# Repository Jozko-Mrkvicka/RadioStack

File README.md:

TODO
====
- Software AVR:
	- Change folder structure in some more sensible way.
	- Polish header files + including.
	- I can`t include delay.h to other files than main one. Find out why and replace all workarounds.
	- Add keyword const to all function declarations where possible.
	- Add description to all functions and describe all input and output parameters.
	- Add description to all modules.
	- There is potential problem with settings of bits in registers to zero. I do it incorrectly. Fix it!!

- Eagle:
	- ADF:
		- Change ELMA encoder to "normal" (single) one.
		- Display will be selected with push button on encoder.
		- Decimal point will define which display is currently selected.
		- Adjust DWG accordingly
		- Draw first board.
		- Think about second board (find out how many more IO modules can be added to the address space).

- Buy:
	- Jumpers.
	- Female pin headers with long pins.

- Other ideas:
	- ELMA encoders not fully working in one NavComm module. Probably mechanically damaged. Fix it or resolder.
	- Holes for buttons and knobs on NavComm module are too small. This problem should be already fixed in Eagle/AutoCAD drawings but check it once again.
	- Change front panel to plastic one:
		- It will be thicker. 
		- Add couple of bolts + nuts to attach it firmly to the rest of a module. 
		- It will have also bevelled edges. 
	- Encoder push buttons in NavComm modules not enabled yet. Add them.
	- Change pin headers to another ones with longer pins to create more space between PCB boards. The reason is to create more space for bolts/nuts to attach the device to a box/cover.

- Unsorted legacy mess:
	SVN
	===
	- nahrat vsetky dokumenty z mejlov (a mozno aj mejly samotne) do zlozky Admin
	- pridat vsetky subory eagle.epf na ignor list

	AutoCAD
	=======
	- zistit preco je XPDR tmavsi ako ostatne casti
	- vypatrat ci existuje nieco ako globalne konstanty/parametre, aby som mohol pouzivat rovnaky rozmer vo viacerych vykresoch
	- (XPDR) pridat objekt "obycajny" prepinac (ako bol na starom transponderu)

	Eagle
	=====
	- (niektore) Konektory na doske NavCom_Board_1 a NavCom_Board_2 su vlozene do vrstvy TOP, ale v skutocnosti sa nachadzaju vzadu (BOTTOM). To sposobi ze pri vyrobe sa ich obrysy vytlacia na opacnej strane dosky (tPlaces vs. bPlaces). Preto je treba tieto suciastky prehodit (Mirror) do spravnej vrstvy. 
	- NavComm 2.1/Board 2 - tlacitka T1 az T4 - trojice dierok pre piny su velmi blizko pri sebe, tlacitko nechce zaliezt do dierok (opravit aj v AutoCADe)
	- (nav/comm) mozno by bolo dobre odstranit vyvody na tlacitko "S" z enkoderov ELMA
	- ku kazdemu enkoderu pridat 2 kondenzatory
	- prepisat popisky tlacitiek T1 az T4 na BTN1 az BTN4

	Programovanie
	=============
	- vysvetlit naco sluzi signal Latch Reset
	- presunut radiostack.h zo zlozky modules/include do common/includes, alebo daco podobne

	Kupit
	=====
	- Dutinková lišta BL810GD
	- este jednu Elmu + hmatniky
	- jumpery
	- MCP23016 (2x)
	- 279-RGP0207CHJ470M (16x odpor z Mouseru)
	- dual shaft/dual concentric enkoder (2 channels) - Mouser
	- doniest z domu ockovy kluc kvoli hmatniku na Elmu
	- 2x Avago HDSP-711E

	======================================================================
	// -c		 skompiluje zdrojak ".c" do objektoveho kodu ".o"
	// -Wall	 warning all
	// -pedantic
	// -o 		 pomenuje vystupny subor
	avr-gcc -c pokus.c -Wall -pedantic -o vystup.o

	// zkompiluje a zlinkuje do ".exe"
	avr-gcc pokus.c libkniznica.a

	// -q	quick append - zalozi archiv / prida ".o" subor do archivu
	avr-ar -q libfnc.a fnc3.o

	// -t	zobrazi vsetky ".o" subory v archive
	avr-ar -t libfnc.a

	// -d	delete - vymaze ".o" subor z archivu
	avr-ar -d libfnc.a fnc3.o

	// -p 	typ procesoru (m8, t13, t2313, ...)
	// -c 	typ programatoru (AVRispmkII)
	// -P 	port ku ktoremu je programator pripojeny (usb)
	// -U 	<typ pamate>:<zapis/citanie>:<subor>:<format dat>
	//		<typ pamate>	flash, eeprom, hfuse, lfuse
	//		<zapis/citanie>	r, w
	//		<subor>			nazov suboru, napr. pokus.hex
	//		<format dat>	i (intel)		
	avrdude -p m8 -c avrispmkii -P usb -U flash:w:pokus.hex:i

	avr-gcc -mmcu=atmega8 -o demo.o -c demo.c 
	avr-gcc -mmcu=atmega8 -o demo.elf demo.o
	avr-objcopy -j .text -j .data -O ihex flash.elf flash.hex

	avrdude -p m8 -c AVRispmkII -P usb -U lfuse:w:0xff:m
	avrdude -p m8 -c AVRispmkII -P usb -U hfuse:w:0xd9:m
	avrdude -p m8 -c AVRispmkII -P usb -U flash:w:bin/radiostack.hex:i

	/////////////////////////////////////////////////////////////
	// Timer/Counter Interrupt Mask Register
	// TIMSK = 0x01;

	// iba pokus
	// Timer/Counter Control Register
	// TCCR0 = 0x01;

	// iba pokus
	// Timer/Counter Register - initial value
	// TCNT0 = 0x00;

	ISR (INT0_vect)
	{
		interruption = 1;

		// overflow++;

		// if (overflow < 300)
		// 	inc = 5;

		// else if ((overflow >= 300) && (overflow < 400))
		// 	inc = 4;

		// else if ((overflow >= 400) && (overflow < 500))
		// 	inc = 3;

		// else if ((overflow >= 500) && (overflow < 600))
		// 	inc = 2;

		// else if ((overflow >= 600) /*&& (overflow < 600)*/)
		//  inc = 1;

		// overflow = 0;
	}

	// ISR (TIMER0_OVF_vect)
	// {
	// 	if (overflow < 2000)
	// 		overflow++;
	// }
	/////////////////////////////////////////////////////////////

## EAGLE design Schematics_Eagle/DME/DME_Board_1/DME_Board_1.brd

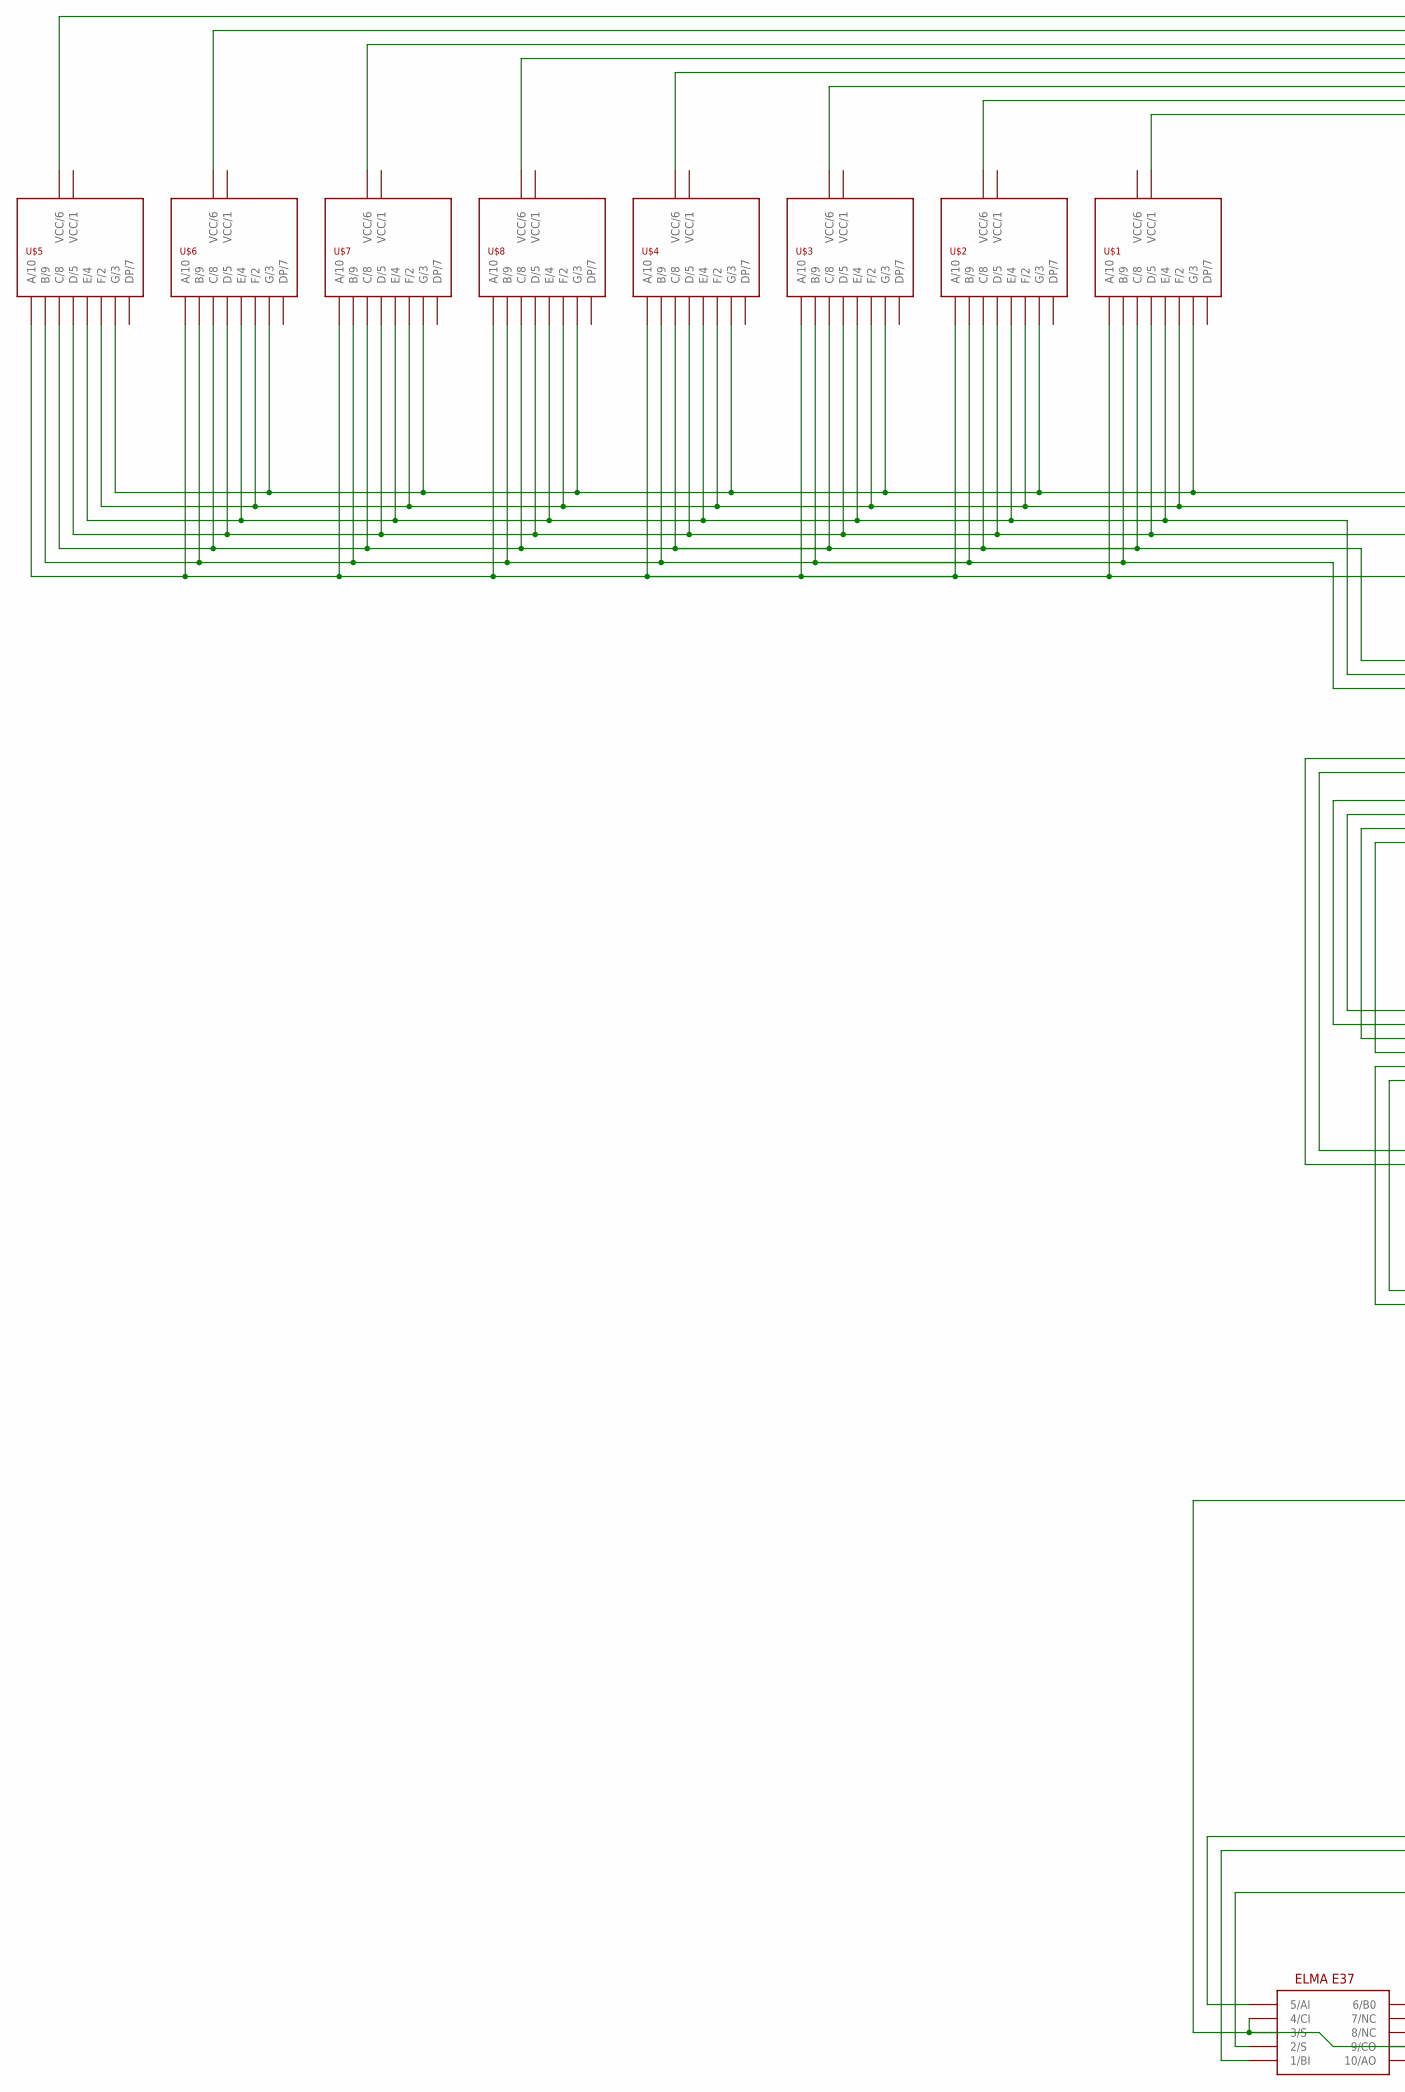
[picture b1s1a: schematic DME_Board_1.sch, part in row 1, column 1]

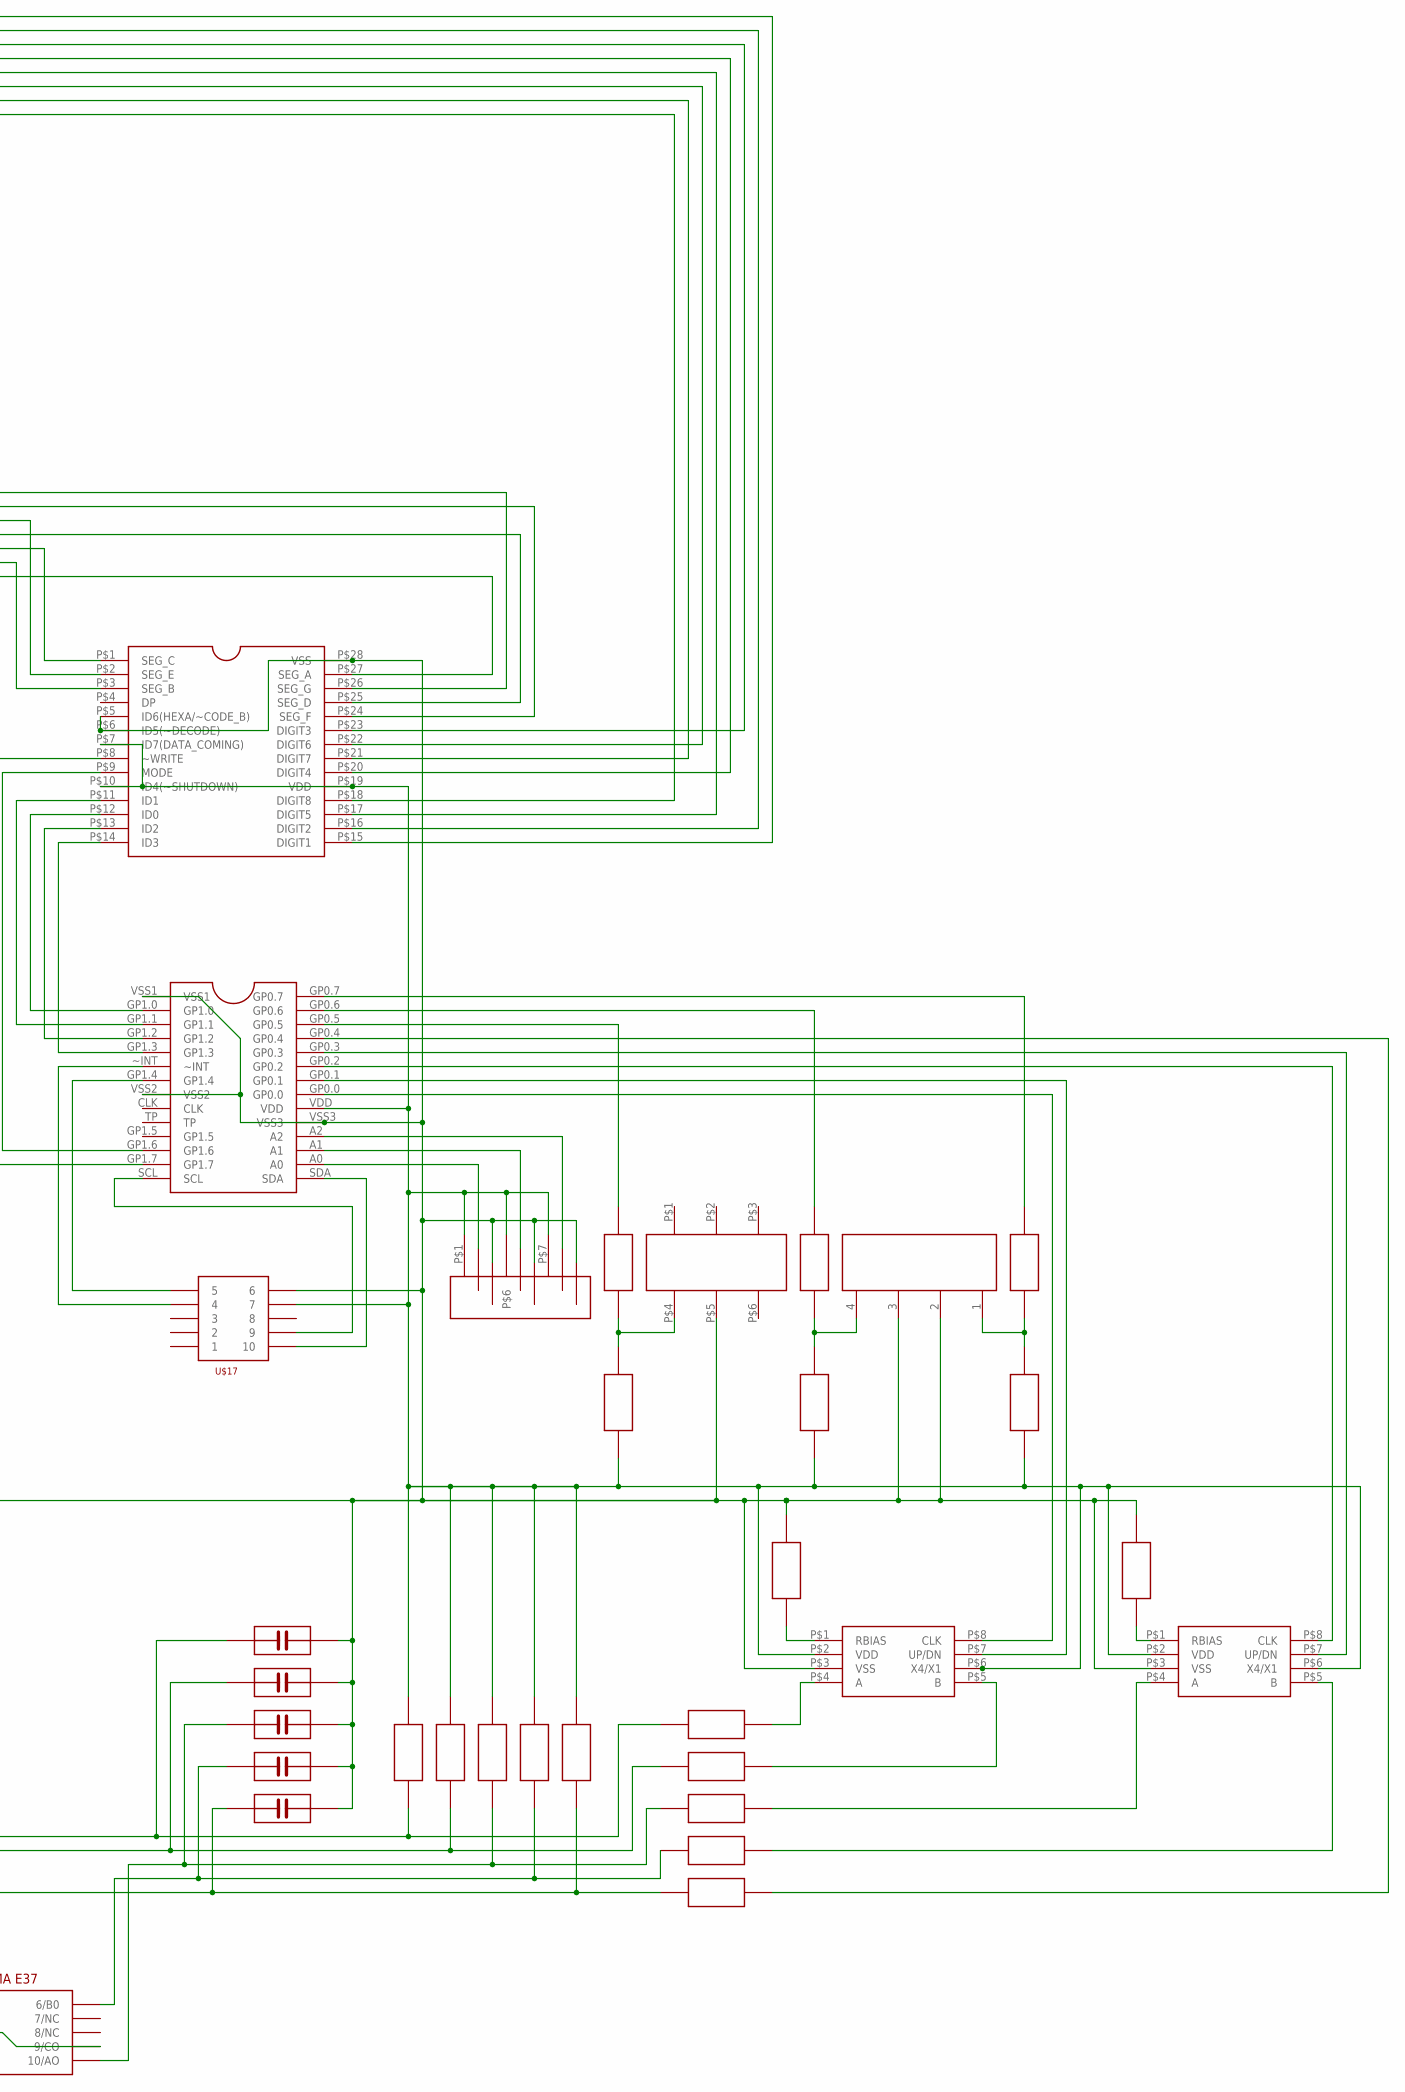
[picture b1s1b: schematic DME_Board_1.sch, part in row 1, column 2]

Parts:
U$1, U$2, U$3, U$4, U$5, U$6, U$7, U$8: SA3611EWA
U$9: ELMA_E37
U$10, U$13, U$15, U$20, U$21, U$22, U$23, U$25, U$26, U$27, U$28, U$29, U$30, U$31, U$32, U$33, U$34, U$35: REZISTOR
U$11, U$42, U$43, U$44: KONDENZATOR
U$12: T220
U$14: ICM7228A
U$16: MCP23016
U$17: LISTA_2X5
U$18, U$46: LS7084
U$19: 46311LD
U$24: ADRESA_0..2
U$45: 103; KONDENZATOR

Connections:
unnamed: U$1.10 (A/10), U$2.10 (A/10), U$3.10 (A/10), U$4.10 (A/10), U$5.10 (A/10), U$6.10 (A/10), U$7.10 (A/10), U$8.10 (A/10), U$14.P$27 (SEG_A)
unnamed: U$1.9 (B/9), U$2.9 (B/9), U$3.9 (B/9), U$4.9 (B/9), U$5.9 (B/9), U$6.9 (B/9), U$7.9 (B/9), U$8.9 (B/9), U$14.P$3 (SEG_B)
unnamed: U$1.8 (C/8), U$2.8 (C/8), U$3.8 (C/8), U$4.8 (C/8), U$5.8 (C/8), U$6.8 (C/8), U$7.8 (C/8), U$8.8 (C/8), U$14.P$1 (SEG_C)
unnamed: U$1.5 (D/5), U$2.5 (D/5), U$3.5 (D/5), U$4.5 (D/5), U$5.5 (D/5), U$6.5 (D/5), U$7.5 (D/5), U$8.5 (D/5), U$14.P$25 (SEG_D)
unnamed: U$5.6 (VCC/6), U$14.P$15 (DIGIT1)
unnamed: U$1.2 (F/2), U$2.2 (F/2), U$3.2 (F/2), U$4.2 (F/2), U$5.2 (F/2), U$6.2 (F/2), U$7.2 (F/2), U$8.2 (F/2), U$14.P$24 (SEG_F)
unnamed: U$1.3 (G/3), U$2.3 (G/3), U$3.3 (G/3), U$4.3 (G/3), U$5.3 (G/3), U$6.3 (G/3), U$7.3 (G/3), U$8.3 (G/3), U$14.P$26 (SEG_G)
unnamed: U$6.6 (VCC/6), U$14.P$16 (DIGIT2)
unnamed: U$1.4 (E/4), U$2.4 (E/4), U$3.4 (E/4), U$4.4 (E/4), U$5.4 (E/4), U$6.4 (E/4), U$7.4 (E/4), U$8.4 (E/4), U$14.P$2 (SEG_E)
unnamed: U$7.6 (VCC/6), U$14.P$23 (DIGIT3)
unnamed: U$8.6 (VCC/6), U$14.P$20 (DIGIT4)
unnamed: U$1.1 (VCC/1), U$14.P$18 (DIGIT8)
unnamed: U$2.6 (VCC/6), U$14.P$21 (DIGIT7)
unnamed: U$3.6 (VCC/6), U$14.P$22 (DIGIT6)
unnamed: U$4.6 (VCC/6), U$14.P$17 (DIGIT5)
unnamed: U$16.GP0.5, U$23.P$2
unnamed: U$9.1 (1/BI), U$11.P$1, U$25.P$1, U$32.P$2
unnamed: U$14.P$12 (ID0), U$16.GP1.0
unnamed: U$14.P$11 (ID1), U$16.GP1.1
unnamed: U$14.P$13 (ID2), U$16.GP1.2
unnamed: U$14.P$14 (ID3), U$16.GP1.3
unnamed: U$14.P$9 (MODE), U$16.GP1.6
unnamed: U$14.P$8 (~WRITE), U$16.GP1.7
unnamed: U$16.A0, U$24.P$2
unnamed: U$10.P$1, U$13.P$1, U$14.P$7 (ID7(DATA_COMING)), U$14.P$10 (ID4(~SHUTDOWN)), U$14.P$19 (VDD), U$15.P$1, U$16.VDD, U$17.7, U$18.P$2 (VDD), U$18.P$6 (X4/X1), U$20.P$2, U$24.P$1, U$24.P$6, U$24.P$7, U$25.P$2, U$26.P$2, U$27.P$2, U$28.P$2, U$46.P$2 (VDD), U$46.P$6 (X4/X1)
unnamed: U$31.P$1, U$46.P$4 (A)
unnamed: U$30.P$1, U$46.P$5 (B)
unnamed: U$9.10 (10/AO), U$26.P$1, U$31.P$2, U$43.P$1
unnamed: U$9.2 (2/S), U$28.P$1, U$29.P$2, U$45.P$1
unnamed: U$9.6 (6/B0), U$27.P$1, U$30.P$2, U$44.P$1
unnamed: U$16.GP0.4, U$29.P$1
unnamed: U$18.P$4 (A), U$33.P$1
unnamed: U$16.A1, U$24.P$5
unnamed: U$35.P$1, U$46.P$1 (RBIAS)
unnamed: U$18.P$5 (B), U$32.P$1
unnamed: U$18.P$1 (RBIAS), U$34.P$1
unnamed: U$16.GP0.1, U$18.P$7 (UP/DN)
unnamed: U$16.GP0.0, U$18.P$8 (CLK)
unnamed: U$16.GP0.3, U$46.P$7 (UP/DN)
unnamed: U$16.GP0.2, U$46.P$8 (CLK)
unnamed: U$9.5 (5/AI), U$20.P$1, U$33.P$2, U$42.P$1
unnamed: U$16.A2, U$24.P$8
unnamed: U$10.P$2, U$12.P$4, U$23.P$1
unnamed: U$9.3 (3/S), U$9.4 (4/CI), U$9.9 (9/CO), U$11.P$2, U$12.P$5, U$14.P$5 (ID6(HEXA/~CODE_B)), U$14.P$6 (ID5(~DECODE)), U$14.P$28 (VSS), U$16.VSS1, U$16.VSS2, U$16.VSS3, U$17.6, U$18.P$3 (VSS), U$19.2, U$19.3, U$24.P$3, U$24.P$4, U$24.P$9, U$34.P$2, U$35.P$2, U$42.P$2, U$43.P$2, U$44.P$2, U$45.P$2, U$46.P$3 (VSS)
unnamed: U$13.P$2, U$19.4, U$22.P$1
unnamed: U$15.P$2, U$19.1, U$21.P$1
unnamed: U$16.GP0.6, U$22.P$2
unnamed: U$16.GP0.7, U$21.P$2
unnamed: U$16.SDA, U$17.10
unnamed: U$16.SCL, U$17.9
unnamed: U$16.GP1.4, U$17.5
unnamed: U$16.~INT, U$17.4

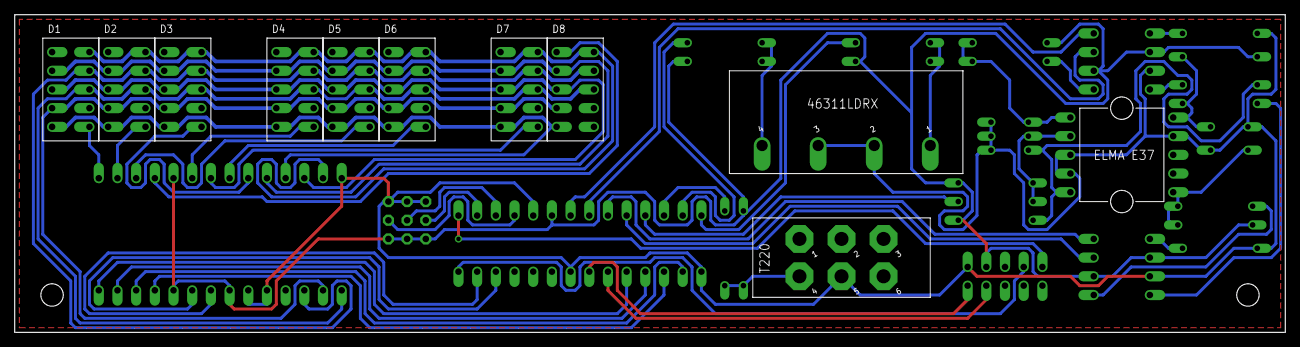
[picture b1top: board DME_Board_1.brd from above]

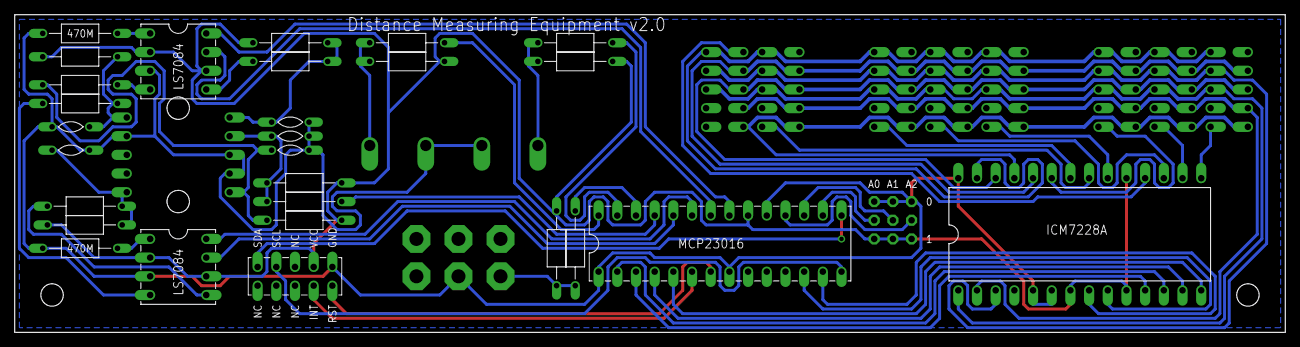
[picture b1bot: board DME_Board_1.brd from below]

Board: 2 copper layers, 172.7 x 43.2 mm, 40 parts (28 on the bottom side), 52 nets.

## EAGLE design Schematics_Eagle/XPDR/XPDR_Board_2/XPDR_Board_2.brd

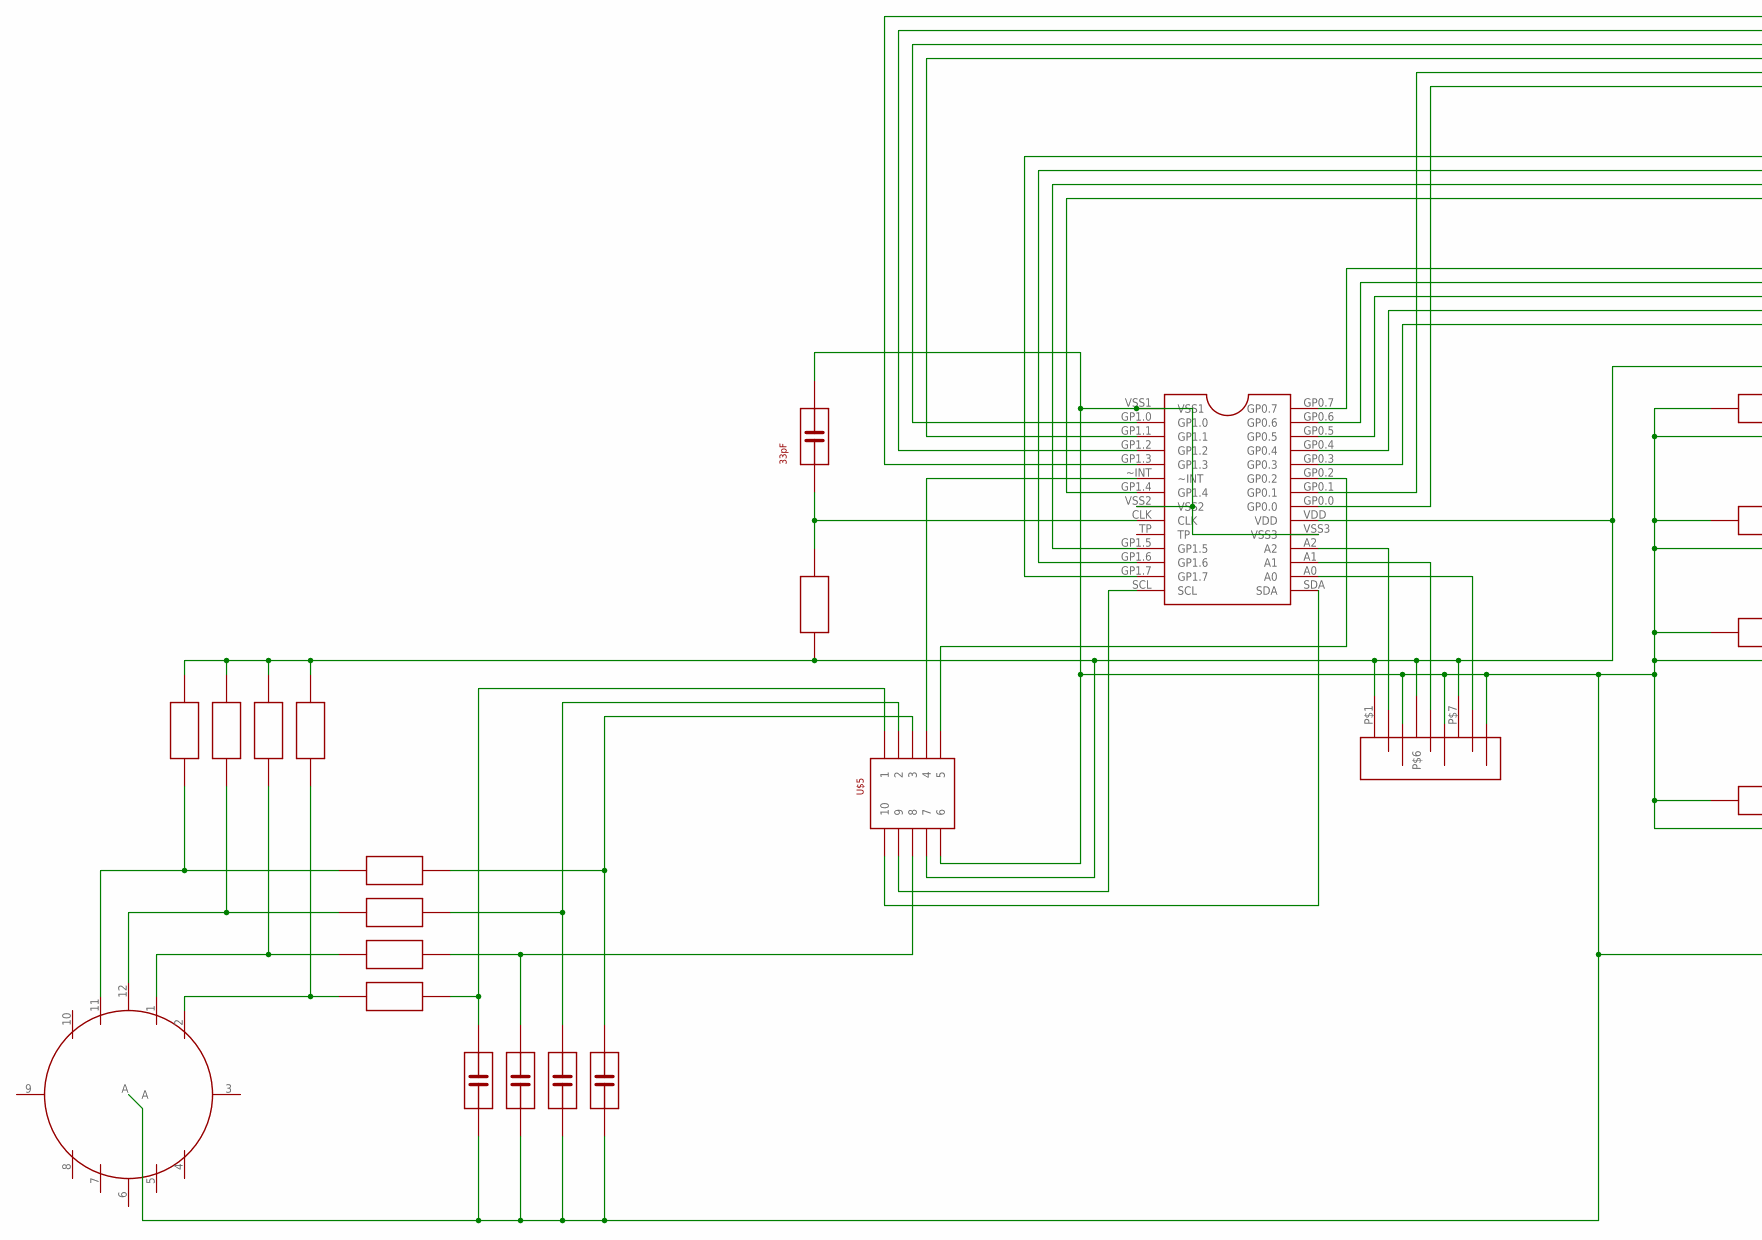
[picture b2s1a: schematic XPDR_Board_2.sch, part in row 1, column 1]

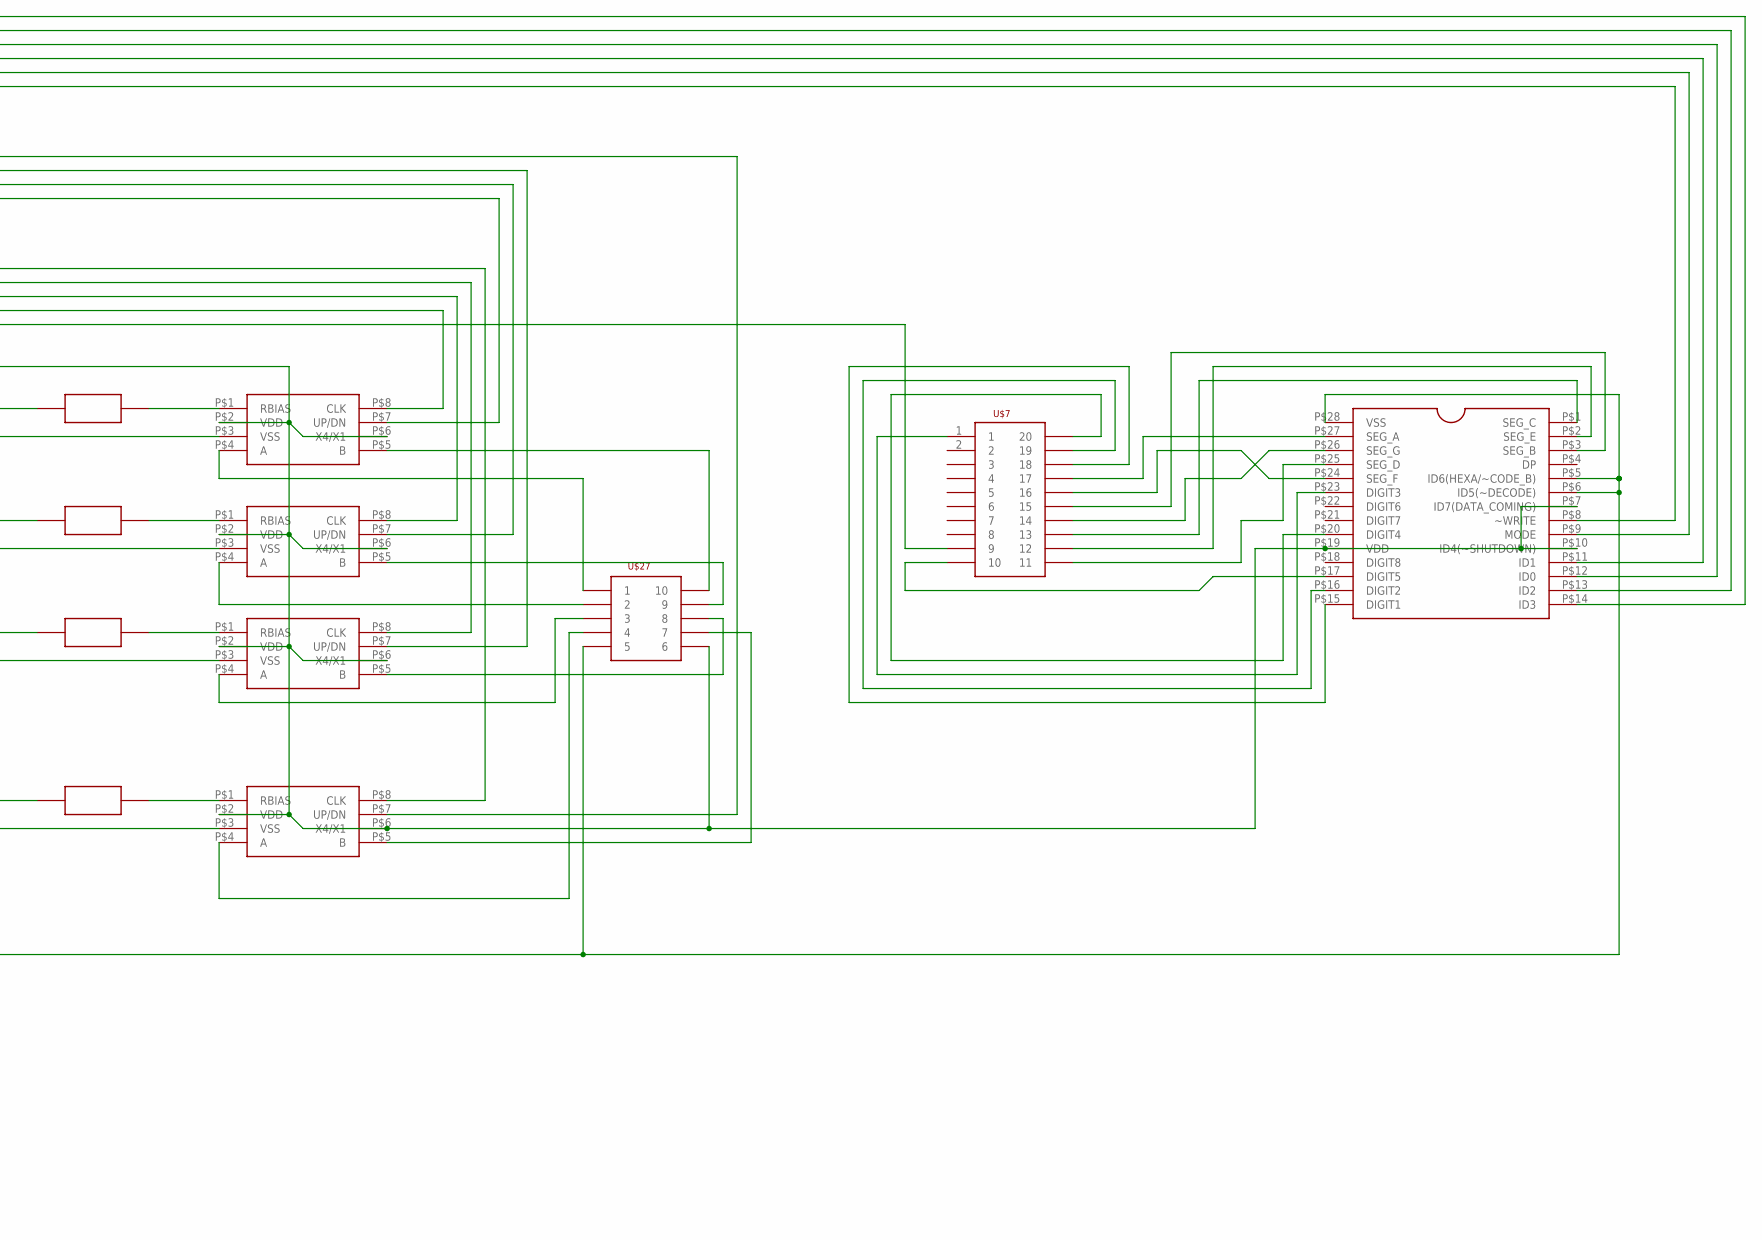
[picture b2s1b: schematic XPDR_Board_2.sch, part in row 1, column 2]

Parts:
U$1, U$2, U$3, U$4: LS7084
U$5, U$27: LISTA_2X5
U$6: ICM7228A
U$7: LISTA_2X10
U$8, U$10, U$12, U$13: 470M; REZISTOR
U$9: MCP23016
U$11: ADRESA_0..2
U$14: 3.9k; REZISTOR
U$15: 33pF; KONDENZATOR
U$16: ROTARY_SWITCH
U$17, U$18, U$19, U$20, U$21, U$22, U$23, U$24: REZISTOR
U$25, U$26, U$28, U$29: KONDENZATOR

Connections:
GND: U$1.P$3 (VSS), U$2.P$3 (VSS), U$3.P$3 (VSS), U$4.P$3 (VSS), U$5.6, U$6.P$5 (ID6(HEXA/~CODE_B)), U$6.P$6 (ID5(~DECODE)), U$6.P$28 (VSS), U$8.P$1, U$9.VSS1, U$9.VSS2, U$9.VSS3, U$10.P$1, U$11.P$3, U$11.P$4, U$11.P$9, U$12.P$1, U$13.P$1, U$15.P$2, U$16.A, U$25.P$1, U$26.P$1, U$27.5, U$28.P$1, U$29.P$1
unnamed: U$6.P$27 (SEG_A), U$7.17
unnamed: U$6.P$24 (SEG_F), U$7.16
unnamed: U$6.P$3 (SEG_B), U$7.15
unnamed: U$6.P$26 (SEG_G), U$7.14
unnamed: U$6.P$1 (SEG_C), U$7.13
unnamed: U$6.P$2 (SEG_E), U$7.12
unnamed: U$6.P$25 (SEG_D), U$7.11
unnamed: U$6.P$15 (DIGIT1), U$7.18
unnamed: U$6.P$16 (DIGIT2), U$7.19
unnamed: U$6.P$23 (DIGIT3), U$7.1
unnamed: U$6.P$20 (DIGIT4), U$7.20
unnamed: U$1.P$2 (VDD), U$1.P$6 (X4/X1), U$2.P$2 (VDD), U$2.P$6 (X4/X1), U$3.P$2 (VDD), U$3.P$6 (X4/X1), U$4.P$2 (VDD), U$4.P$6 (X4/X1), U$5.7, U$6.P$7 (ID7(DATA_COMING)), U$6.P$10 (ID4(~SHUTDOWN)), U$6.P$19 (VDD), U$9.VDD, U$11.P$1, U$11.P$6, U$11.P$7, U$14.P$1, U$17.P$1, U$18.P$1, U$19.P$1, U$20.P$1, U$27.6
unnamed: U$6.P$12 (ID0), U$9.GP1.0
unnamed: U$1.P$8 (CLK), U$9.GP0.4
unnamed: U$2.P$8 (CLK), U$9.GP0.5
unnamed: U$1.P$1 (RBIAS), U$8.P$2
unnamed: U$2.P$1 (RBIAS), U$10.P$2
unnamed: U$3.P$1 (RBIAS), U$12.P$2
unnamed: U$4.P$1 (RBIAS), U$13.P$2
unnamed: U$6.P$11 (ID1), U$9.GP1.1
unnamed: U$3.P$8 (CLK), U$9.GP0.6
unnamed: U$4.P$8 (CLK), U$9.GP0.7
unnamed: U$1.P$7 (UP/DN), U$9.GP1.4
unnamed: U$1.P$4 (A), U$27.1
unnamed: U$1.P$5 (B), U$27.10
unnamed: U$2.P$4 (A), U$27.2
unnamed: U$2.P$5 (B), U$27.9
unnamed: U$3.P$4 (A), U$27.3
unnamed: U$3.P$5 (B), U$27.8
unnamed: U$4.P$4 (A), U$27.4
unnamed: U$4.P$5 (B), U$27.7
unnamed: U$2.P$7 (UP/DN), U$9.GP1.5
unnamed: U$3.P$7 (UP/DN), U$9.GP1.6
unnamed: U$4.P$7 (UP/DN), U$9.GP1.7
unnamed: U$9.A0, U$11.P$8
unnamed: U$9.A1, U$11.P$5
unnamed: U$9.A2, U$11.P$2
unnamed: U$6.P$13 (ID2), U$9.GP1.2
unnamed: U$6.P$14 (ID3), U$9.GP1.3
unnamed: U$16.11, U$17.P$2, U$21.P$2
unnamed: U$6.P$8 (~WRITE), U$9.GP0.0
unnamed: U$6.P$9 (MODE), U$9.GP0.1
unnamed: U$16.12, U$18.P$2, U$22.P$2
unnamed: U$5.9, U$9.SCL
unnamed: U$5.10, U$9.SDA
unnamed: U$5.4, U$9.~INT
unnamed: U$5.5, U$9.GP0.2
unnamed: U$9.CLK, U$14.P$2, U$15.P$1
unnamed: U$7.9, U$9.GP0.3
unnamed: U$6.P$17 (DIGIT5), U$7.10
unnamed: U$16.1, U$19.P$2, U$23.P$2
unnamed: U$16.2, U$20.P$2, U$24.P$2
unnamed: U$5.8, U$23.P$1, U$26.P$2
unnamed: U$5.2, U$22.P$1, U$28.P$2
unnamed: U$5.3, U$21.P$1, U$29.P$2
unnamed: U$5.1, U$24.P$1, U$25.P$2

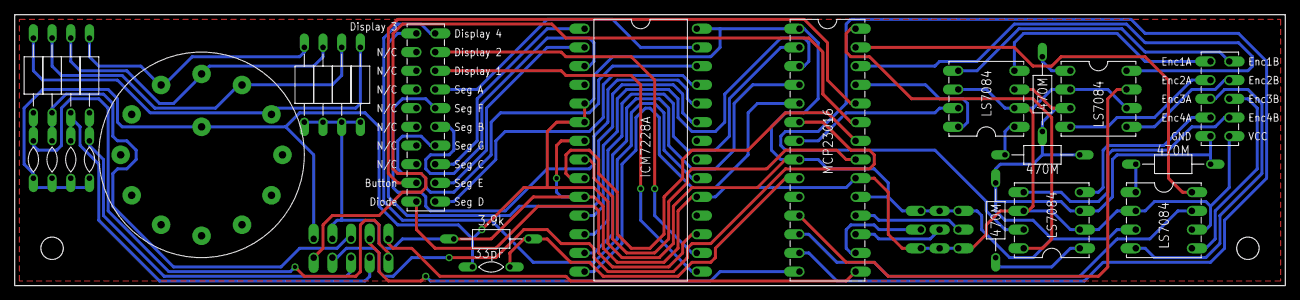
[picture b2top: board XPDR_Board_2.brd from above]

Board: 2 copper layers, 172.7 x 36.8 mm, 29 parts (1 on the bottom side), 57 nets.

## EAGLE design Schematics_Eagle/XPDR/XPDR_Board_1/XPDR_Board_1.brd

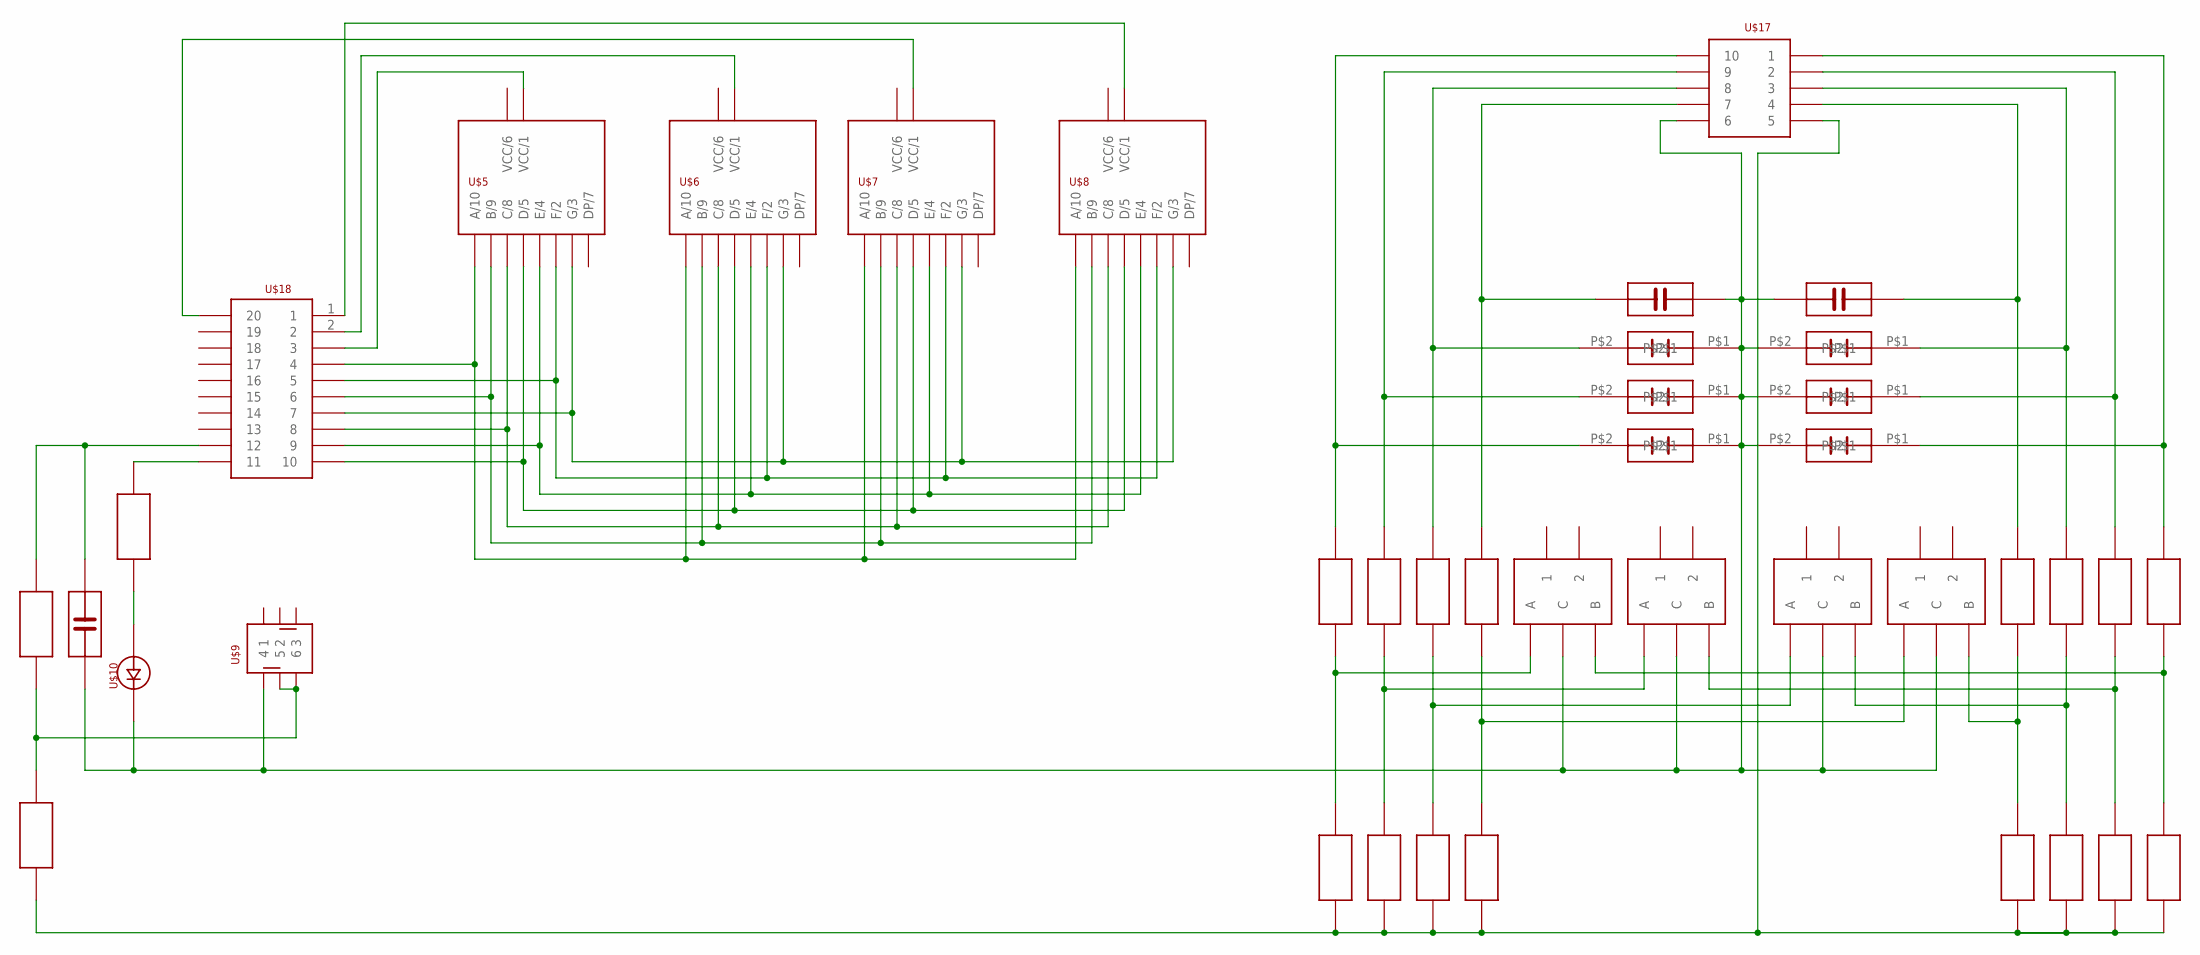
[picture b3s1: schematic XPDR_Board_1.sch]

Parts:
U$1, U$2, U$3, U$4: PEC11R
U$5, U$6, U$7, U$8: SA3611EWA
U$9: P1-0S
U$10: LED_5MM
U$11, U$12, U$13, U$14, U$15, U$16, U$19, U$20, U$21, U$22, U$23, U$24, U$25, U$26, U$27, U$28, U$30, U$31, U$40: REZISTOR
U$17: LISTA_2X5
U$18: LISTA_2X10
U$29, U$32, U$33, U$35, U$36, U$37: KONDENZATOR_SIROKY
U$34, U$38, U$39: KONDENZATOR

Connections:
unnamed: U$5.10 (A/10), U$6.10 (A/10), U$7.10 (A/10), U$8.10 (A/10), U$18.4
unnamed: U$5.9 (B/9), U$6.9 (B/9), U$7.9 (B/9), U$8.9 (B/9), U$18.6
unnamed: U$5.8 (C/8), U$6.8 (C/8), U$7.8 (C/8), U$8.8 (C/8), U$18.8
unnamed: U$5.5 (D/5), U$6.5 (D/5), U$7.5 (D/5), U$8.5 (D/5), U$18.10
unnamed: U$11.P$2, U$17.10, U$29.P$2
unnamed: U$5.2 (F/2), U$6.2 (F/2), U$7.2 (F/2), U$8.2 (F/2), U$18.5
unnamed: U$5.3 (G/3), U$6.3 (G/3), U$7.3 (G/3), U$8.3 (G/3), U$18.7
unnamed: U$1.B, U$12.P$1, U$27.P$1
unnamed: U$5.4 (E/4), U$6.4 (E/4), U$7.4 (E/4), U$8.4 (E/4), U$18.9
unnamed: U$13.P$2, U$17.9, U$32.P$2
unnamed: U$2.B, U$14.P$1, U$25.P$1
unnamed: U$15.P$2, U$17.8, U$33.P$2
unnamed: U$3.B, U$16.P$1, U$23.P$1
unnamed: U$17.7, U$19.P$2, U$34.P$2
unnamed: U$4.B, U$20.P$1, U$21.P$1
unnamed: U$5.1 (VCC/1), U$18.3
unnamed: U$6.1 (VCC/1), U$18.2
unnamed: U$7.1 (VCC/1), U$18.20
unnamed: U$8.1 (VCC/1), U$18.1
unnamed: U$9.5, U$9.6, U$30.P$2, U$31.P$1
unnamed: U$1.C, U$2.C, U$3.C, U$4.C, U$9.4, U$10.P$2, U$17.6, U$29.P$1, U$32.P$1, U$33.P$1, U$34.P$1, U$35.P$2, U$36.P$2, U$37.P$2, U$38.P$2, U$39.P$2
unnamed: U$1.A, U$11.P$1, U$28.P$1
unnamed: U$12.P$2, U$17.1, U$35.P$1
unnamed: U$17.5, U$21.P$2, U$22.P$2, U$23.P$2, U$24.P$2, U$25.P$2, U$26.P$2, U$27.P$2, U$28.P$2, U$31.P$2
unnamed: U$3.A, U$15.P$1, U$24.P$1
unnamed: U$18.11, U$40.P$1
unnamed: U$4.A, U$19.P$1, U$22.P$1
unnamed: U$14.P$2, U$17.2, U$36.P$1
unnamed: U$16.P$2, U$17.3, U$37.P$1
unnamed: U$17.4, U$20.P$2, U$38.P$1
unnamed: U$2.A, U$13.P$1, U$26.P$1
unnamed: U$10.P$1, U$40.P$2
unnamed: U$18.12, U$30.P$1, U$39.P$1

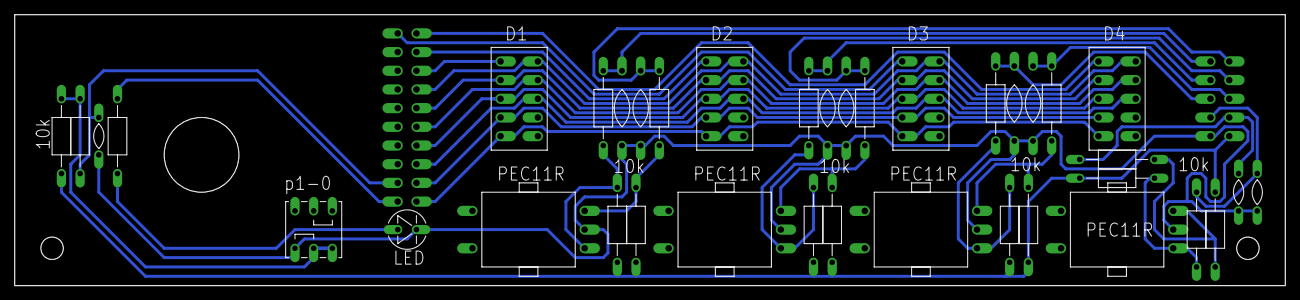
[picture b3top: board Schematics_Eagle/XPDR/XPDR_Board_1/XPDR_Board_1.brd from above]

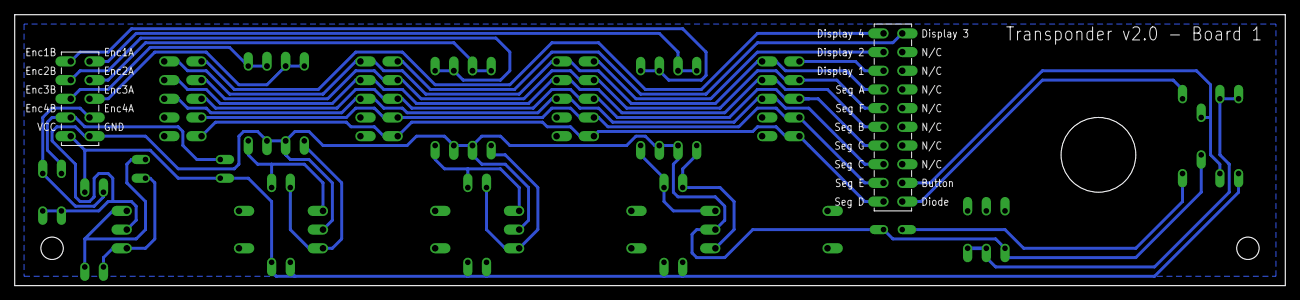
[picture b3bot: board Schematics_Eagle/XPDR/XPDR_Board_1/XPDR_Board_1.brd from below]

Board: 2 copper layers, 172.7 x 36.8 mm, 40 parts (2 on the bottom side), 33 nets.
